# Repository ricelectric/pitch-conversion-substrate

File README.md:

# pitch-conversion-substrate

This is an open source repository for a pitch conversion substrate for ESP32-C3. More information is available [here](https://qiita.com/ricelectric/items/3a3d29f45651f7c7f38b).

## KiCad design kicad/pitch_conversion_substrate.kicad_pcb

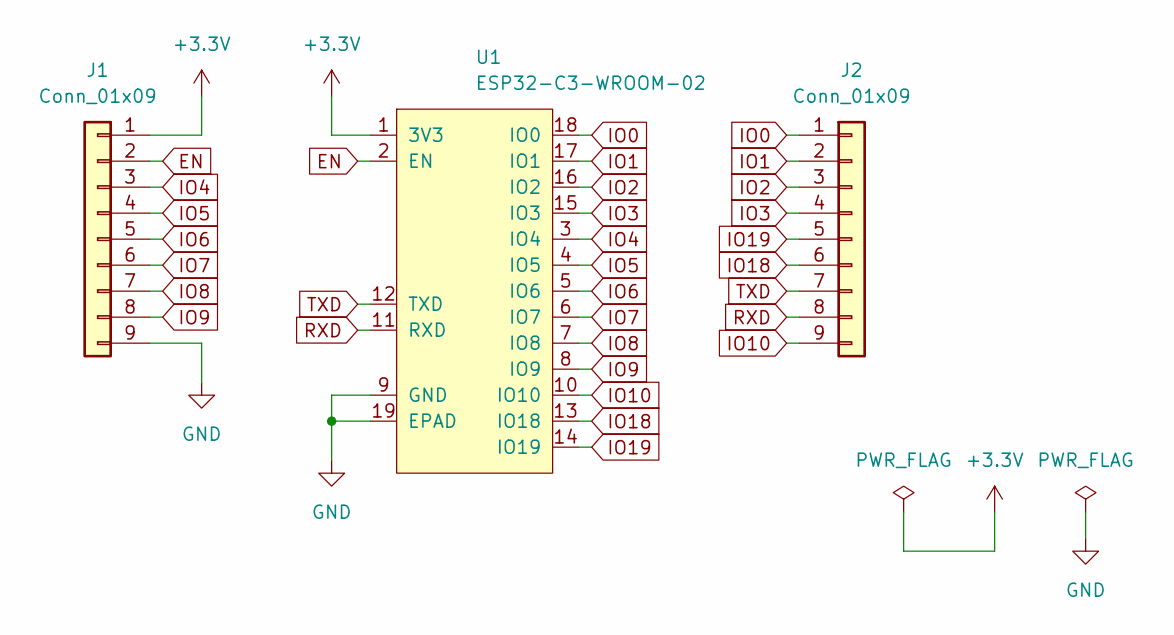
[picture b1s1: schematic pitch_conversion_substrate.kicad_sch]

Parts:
J1, J2: Conn_01x09; PinHeader_1x09_P2.54mm_Vertical
U1: ESP32-C3-WROOM-02

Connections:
+3.3V: J1.1, U1.1 (3V3)
EN: J1.2, U1.2 (EN)
GND: J1.9, U1.9 (GND), U1.19 (EPAD)
IO0: J2.1, U1.18 (IO0)
IO1: J2.2, U1.17 (IO1)
IO2: J2.3, U1.16 (IO2)
IO3: J2.4, U1.15 (IO3)
IO4: J1.3, U1.3 (IO4)
IO5: J1.4, U1.4 (IO5)
IO6: J1.5, U1.5 (IO6)
IO7: J1.6, U1.6 (IO7)
IO8: J1.7, U1.7 (IO8)
IO9: J1.8, U1.8 (IO9)
IO10: J2.9, U1.10 (IO10)
IO18: J2.6, U1.13 (IO18)
IO19: J2.5, U1.14 (IO19)
RXD: J2.8, U1.11 (RXD)
TXD: J2.7, U1.12 (TXD)

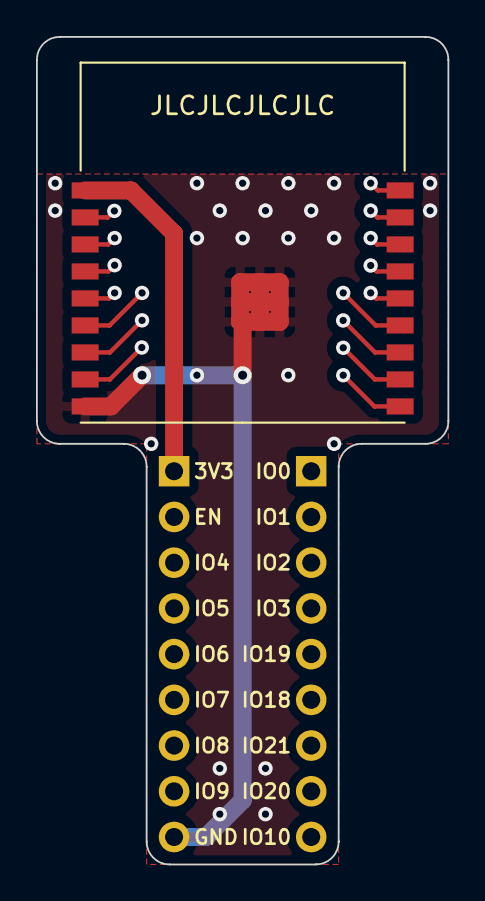
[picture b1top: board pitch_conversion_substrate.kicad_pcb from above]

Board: 4 copper layers, 22.9 x 46.0 mm, 3 parts (0 on the bottom side), 18 nets.
